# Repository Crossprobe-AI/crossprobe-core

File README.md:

# Crossprobe

A KiCad editor that runs in the browser. Open a KiCad project folder, view and
edit its schematic and board, and save it back as KiCad files: unmodified files
are written back byte for byte, and edits produce minimal diffs. The goal is
parity with KiCad: its behaviour is reimplemented in TypeScript and checked against
what KiCad itself does with the same projects.

Try it in your browser: <https://core.crossprobe.ai>, the editor from this
repository as it is. Files stay on your computer there too.

On a phone, the editor is a viewer: the schematic, the board and the 3D view, a tap on a part
for what it is, pinch to zoom.

## What it does

- Schematic, PCB and 3D views, with cross-probing between them.
- Schematic editing: wires, labels, buses, hierarchical sheets, parts from KiCad's
  libraries, annotation, ERC.
- PCB editing: placement, interactive routing (45° tracks, vias, differential pairs,
  length tuning), zones, Update PCB from schematic, DRC, schematic ↔ board parity.
- Symbol and footprint editors; plotting; fabrication outputs (Gerber, drill, BOM,
  pick-and-place, IPC-2581, ODB++, STEP, GLB).
- [Design blocks](blocks/README.md) (reference circuits with cited checklists),
  [requirements](docs/requirements.md) and [compatibility](docs/compatibility.md)
  checks, and datasheet evidence pinned to parts.

What works and what doesn't yet, feature by feature: [KiCad parity](#kicad-parity).

## Run it

With Docker ([docs/docker.md](docs/docker.md)):

```sh
docker compose up --build
```

Then open <http://localhost:5173> in Chrome, Edge or another Chromium browser and
choose your project's folder. Files stay on your computer: the browser reads the
folder and saves into it.

Without Docker, with Node.js 22.12 or later (KiCad's libraries are read from a KiCad
installation, or from `KICAD_SYMBOLS`, `KICAD_FOOTPRINTS` and `KICAD_DEMOS`):

```sh
npm ci
npm run dev         # the app at http://localhost:5173
```

To host it, build static files with `npm run build -w @crossprobe/web` (they land in
`apps/web/dist`). A build is served under `/app/`. Set `CROSSPROBE_BASE=/` to serve
it at the root of its own domain instead. The KiCad libraries are fetched from
`/__demos/…`, which the dev server answers; a static host has to provide them.

## Develop

How to contribute, and the rules a change follows: [CONTRIBUTING.md](CONTRIBUTING.md).
Bugs and requests: [GitHub Issues](https://github.com/Crossprobe-AI/crossprobe-core/issues). Security problems: privately, as
[SECURITY.md](SECURITY.md) says.

```sh
npm run build       # @crossprobe/kicad-sexpr and @crossprobe/kicad-model
npm run typecheck   # the app and its UI component tests
npm test
```

| Path | What it is |
|---|---|
| [`packages/kicad-sexpr`](packages/kicad-sexpr) | Lossless parser and writer for every KiCad S-expression format, with KiCad-style editing helpers |
| [`packages/kicad-model`](packages/kicad-model) | The design model: schematic hierarchy and nets as KiCad sees them, the board, ERC, DRC, parity, editing, fabrication outputs, design blocks |
| [`apps/web`](apps/web) | The browser app |
| [`apps/web/src/extensions`](apps/web/src/extensions/api.ts) | The editor's extension points: inspector tabs, places to open and keep projects, sections of the Review tab |

Many tests compare results with KiCad's own on its demo projects, and skip when
KiCad or the demos are missing. KiCad and its libraries are found in the usual
places on macOS and Linux ([test-setup.ts](test-setup.ts)). The demos are not
part of every installer: they are the `demos` folder of KiCad's source, so point
the tests at a copy.

| Variable | What it points at |
|---|---|
| `KICAD_CLI` | KiCad's command-line program, when it is not in the usual place |
| `KICAD_DEMOS` | KiCad's demo projects |
| `KICAD_CORPUS` | A folder of other projects to compare on, in place of the demos (the file round trip takes several, colon-separated) |
| `KICAD_QA` | The `qa/data` folder of KiCad's source, for the netlist edge cases |

The tests that compare with KiCad don't run on GitHub (the runner has no
KiCad): run `npm test` with the demos before changing the model, the checks or
the exports. The browser scripts in `scripts/e2e-*.mjs` drive the app end to
end ([docs/end-to-end.md](docs/end-to-end.md)).

The editor's shared controls (the top bar's menus, the inspector's tab bar,
Save) have component tests in `apps/web/test/ui/*.test.tsx`. They run in
headless Chromium with the app's stylesheet (Vitest's browser mode), so layout,
focus, keyboard and clicks are the real ones. `npm test` runs them with the rest;
the first time, install the browser with `npx playwright install chromium`.
`npx vitest --project ui` runs only them.

Commit messages follow [Conventional Commits](https://www.conventionalcommits.org)
(`fix:`, `feat:`, `feat!:` for a breaking change, and `docs:`, `test:`, `ci:`
for the rest). Releases are made from them: each push to `main` updates a release
pull request with the next version and the changelog, and merging it tags
`vX.Y.Z` and publishes the release
([release.yml](.github/workflows/release.yml)).

## KiCad parity

What a KiCad user can expect, compared with KiCad 9 and 10. The comparisons were
last run with KiCad 10.0.5. Update this list in the same change that adds or
completes a feature.

- **Works**: implemented, and checked against KiCad (a test or an end-to-end
  script compares the result with what KiCad gives for the same project).
- **Partly**: usable, with the limits given.
- **View only**: existing items are read, drawn, plotted and kept on save, but
  can't be made or changed here.
- **No**: not there. Unless noted, such items in an existing file are left
  untouched when you save, but are not shown.

### Files and projects

| Feature | Status | Notes |
|---|---|---|
| `.kicad_sch`, `.kicad_pcb` read and write | Works | Unchanged files are written back byte for byte; edits change only the lines they touch |
| Project symbol and footprint libraries (`.kicad_sym`, `.pretty`) | Works | Derived symbols are resolved |
| `.kicad_pro` | Partly | Net classes, design-rule minimums, severities, DRC exclusions and the pin conflict map are read and written; other settings are kept, with no way to edit them |
| New project, open a folder, save in place | Works | Saving in place needs a Chromium browser; others download the changed files. New files are written as KiCad 10 |
| Unsaved changes survive a reload | Works | |
| File versions before KiCad 9 | Works | KiCad 6, 7 and 8 files are read: every file in KiCad's own test data is written back byte for byte, and netlists (of annotated designs) and IPC-D-356 files match KiCad's on them. Edited and saved, all 113 of its files from before KiCad 8 are read by KiCad with every edit, and give KiCad's netlist |
| KiCad's installed libraries (symbols, footprints, 3D models) | Partly | Served by the dev server or the Docker image; your own path variables are not resolved |
| Library tables | Partly | Project tables with `${KIPRJMOD}` entries; no table editor |
| Custom design rules (`.kicad_dru`) | Partly | Read and applied for some constraints (see PCB editor); no editor |
| Text variables (`${REVISION}`, `${REFERENCE}`, project variables) | Partly | In the schematic, shown, plotted and netlisted as KiCad resolves them: the title block, sheet and project variables, a part's own fields, another part's (`${R1:VALUE}`). Not the net, pin and simulation variables (`${NET_NAME(1)}`, `${OP}`); on the board they are shown as written. No editor for project variables |
| Custom drawing sheets (`.kicad_wks`) | Partly | The project's sheet is drawn and plotted on every schematic page, its texts where KiCad puts them (checked on KiCad's templates and demos). Logos (PNG or JPEG) included. Chosen in KiCad: no picker here, no drawing sheet editor. The board view draws its own sheet (pcbnew's, from the project) around the board, with the board's title block, the project's text variables (as KiCad's board plot shows them) and a "Drawing sheet" visibility toggle; board plots leave it out. Both paths are resolved as KiCad does: `${KIPRJMOD}` and the project's text variables, relative or absolute into the project folder. A sheet outside the project folder (KiCad's template folder, say) can't be read in the browser. Without one, a default frame is drawn, its title block with the project's variables |
| Legacy formats (`.sch`, `.brd`, `.lib`), importers (Eagle, Altium, EasyEDA, …) | No | |
| Design variants, jobsets, embedded files, project templates and archives | No | |

### Schematic editor

| Feature | Status | Notes |
|---|---|---|
| Connectivity and net names as KiCad computes them | Works | Compared pin for pin and name for name with KiCad's netlist: hierarchy, buses, jumper pins and stacked pin numbers included |
| Wires, junctions, no-connects | Works | Dragging keeps connections |
| Buses, bus entries, vector buses | Works | Bus aliases are read; they can't be defined here |
| Local and hierarchical labels | Works | |
| Global labels | Works | With the shape (input, output, …) |
| Power symbols, PWR_FLAG | Works | |
| Hierarchical sheets and sheet pins | Works | A selected sheet symbol is renamed, given a page number, and its pins synchronised with the labels inside. Its file can't be changed, and its pins can't be moved or deleted one by one |
| Placing symbols from project and KiCad libraries | Works | |
| Multi-unit symbols | Works | |
| Body styles (De Morgan) | Works | Made in the symbol editor; a placed symbol is switched in the inspector |
| Alternate pin functions | Works | Defined per pin in the symbol editor (name, type, shape); a placed symbol's pin is switched in the inspector, and the sheet, ERC and netlist follow |
| Move, rotate, mirror, delete, box select, copy, paste, duplicate | Works | Its own clipboard: not the system's, not between projects |
| Undo and redo | Works | |
| Fields, and the symbol fields table | Works | A field on the sheet is dragged, turned (R) and edited (double-click) on its own, and shown or hidden in the inspector. No font or justification settings, no autoplace; no BOM presets |
| DNP, exclude from BOM, exclude from board, exclude from simulation | Works | A part not populated is crossed out, on the sheet and in plots |
| Annotation | Works | The whole schematic or one sheet; new parts only or all, by X or Y; from a start number or the sheet number × 100 or × 1000; clear annotation. No selection scope |
| Footprint assignment | Works | Filtered by the symbol's footprint filters and pin count |
| Text, text boxes, lines, rectangles, circles, arcs | Works | No font or style settings; beziers are view only |
| Images | Works | Placed with the Image tool (other formats become PNG, as KiCad stores them), moved, and sized; KiCad reads them back unchanged |
| Intersheet references | Works | The pages a global label is on, as KiCad lists them (own page, short form, prefix and suffix), switched on in Page settings; drawn where KiCad places them, not movable |
| Net class directives, rule areas | Works | Placed on wires and buses, or on a rule area's outline for everything inside; a label's Netclass field counts too. Nets get KiCad's classes, combined ones included ("A,Default"), and the project file keeps them as KiCad does. Only the Netclass field: no component classes |
| Tables | Works | Drawn as KiCad draws them (border, header line, separators, spans, text justified in each cell); placed with the Table tool (on sheets from KiCad 9 on), cells filled in by double-click, moved and box-selected as a whole, KiCad 9's tables (no UUID) too. Rows, columns and spans can't be changed here |
| Hyperlinks | Works | On texts and labels: a web address or a page (`#2`), opened with a click when not editing; set with Link… on a selected text. Not on fields or in plots |
| Find and replace | Works | Ctrl+F: texts, text boxes, labels, sheet names and pins, and fields, on every sheet; match case, whole words, wildcards, references, hidden fields. Replace all is one undo step. Not pin names or numbers |
| Cross-probing and net highlighting | Works | Between schematic, board and 3D |
| ERC | Partly | 33 checks, at least 98% agreement with KiCad on its demos, and 89% of KiCad's findings on the edge cases in its own test data: pin conflicts (with the project's pin map), undriven and unconnected pins, no-connect, label, wire, off-grid, multiple net names, similar labels, duplicate references, sheet pins and hierarchical labels without a partner, unplaced units (and their input, supply and bidirectional pins), units with different footprints, duplicate sheet names, a local label named like a global one, unresolved text variables (in texts), a global label that appears once, labels and power nets that differ only in case, field names with spaces around them. undefined net classes, a pin shared by a part's units on different nets, a ground pin off the ground net, a net label on a bus or a bus label on a wire, a wire through a bus entry that isn't one of the bus's members, two names on one bus. Not checked: bus-to-bus conflicts, bus alias conflicts, library and footprint link issues. Severities are read from the project. Findings can be excluded with a reason, kept in the project file as KiCad does: KiCad honours ours where the finding's items have UUIDs here (labels, pins), and we honour KiCad's by check, place and sheet |
| Netlist export | Works | KiCad's format (`.net`): the same parts, fields, nets and pins as `kicad-cli` writes on its demos. A net in several classes names the first. Not the OrcadPCB2, CadStar, Allegro, PADS, SPICE or XML formats |
| SPICE simulation | No | |
| Design blocks | Works | Inserts the blocks in `blocks/` and the project's own; a selection is saved as a block in the project's block library, in KiCad's layout (`<project>.kicad_blocks`, `design-block-lib-table`). No block library editor; blocks from other libraries in the table are not listed |
| Page settings and title block | Works | |
| Plot to SVG and PDF | Works | PDF through the browser's print dialog. No PostScript, DXF or HPGL |

### PCB editor

| Feature | Status | Notes |
|---|---|---|
| Place, move, rotate, flip, lock footprints | Works | Compared with KiCad's result for the same move |
| Update PCB from schematic, update schematic from PCB | Works | |
| Update footprints from the library | Works | |
| Schematic ↔ board parity, ratsnest | Works | A few zone-to-pad cases over-report unconnected items |
| Copper layer count, design-rule minimums, net classes | Works | With presets for KiCad's defaults and JLCPCB. A net in several classes (by pattern or from the schematic) combines them by priority, with Default filling what they leave unset, as KiCad 10 does |
| Stackup | Partly | Read and used; written only from the presets; no editor |
| Custom rules | Partly | `clearance`, `hole_size`, `annular_width`, `track_width`, `via_diameter`, `length` and `skew` (with `fromTo` between parts; skew `within_diff_pairs` too), `diff_pair_gap` and `diff_pair_uncoupled`, `connection_width`, with the common condition functions. Lengths between parts can differ from KiCad's by up to ~0.7 mm on some routes, so findings near a limit may differ; differential pair gaps and uncoupled lengths equal KiCad's. Not: edge, silk and courtyard clearance, `disallow` |
| Interactive routing with 45° tracks | Works | Posture, width, via and layer change while routing |
| Router modes | Partly | Highlight collisions and walkaround work; shove moves up to three tracks, along the grid |
| Arc tracks | View only | Drawn, measured and plotted; can't be routed |
| Dragging tracks | Partly | Track ends, and tracks follow a moved footprint; no segment drag |
| Vias: through, blind, buried, micro | Works | No tenting or via-in-pad options |
| Differential pairs | Partly | Coupled routing with paired vias; they don't shove |
| Length tuning | Partly | Single-track meanders to a target, and matching a pair; not saved as KiCad tuning patterns |
| Teardrops | Partly | Straight-edged; all or none |
| Zones: draw, fill, refill | Works | Priorities, thermal reliefs, island removal and keepouts are honoured; fills compared with KiCad's by area and by its DRC |
| Zone properties | Partly | Net, layer, pad connection, name, priority, clearance, minimum width, thermal gap and spoke width, island removal: edited in the properties panel, honoured by the fill, and read back by KiCad as set. Hatched fills (line width, gap, angle; KiCad's hole smoothing and minimum hole area as read) are filled as KiCad fills them, thermal rings round reliefs and same-net vias relieved too: on a demo zone made hatched, our copper differs from KiCad's by about as much as the solid fill does. Multi-layer zones keep their layer set; no corner smoothing or per-layer properties (nor per-layer hatch offsets) |
| Point editing of zones and shapes | Works | KiCad's handles on a selected zone, polygon, line, rectangle, circle or arc: corners, and edge middles that move an edge with its corners sliding along the neighbours; Add Corner and Remove Corner from the right-click menu. Outlines KiCad reads back as edited. Only a zone's first outline; no chamfer or fillet of corners |
| Keepout and rule areas | View only | Honoured by the fill, the DRC and custom rules |
| Board outline | Works | Rectangle, rounded rectangle, polygon, mounting holes |
| Graphics on other layers | View only | Movable; no drawing tools beyond the outline |
| Text | Partly | Silkscreen text can be placed and edited; knockout and TrueType text are view only |
| Dimensions | Partly | Aligned and orthogonal can be placed; radial, leader and centre are view only |
| Groups | Works | Group (Ctrl+G) and Ungroup (Ctrl+Shift+G), nested groups; a click selects a part's whole group, which moves, turns (about its centre: the box KiCad gives it, part texts and unmodelled items included, checked against pcbnew), aligns (by that box), locks (L) and deletes together, items the app doesn't model (images, tables, targets) included, locked ones staying; unlocking a group also unlocks its parts locked on their own; deleted items leave their groups and empty groups go. KiCad reads the groups back as made. Copies (duplicate, paste, array) are not grouped; no entering a group to edit one part |
| Text boxes | Works | Drawn with the text box tool (two corners, then the text), shown, plotted and wrapped as KiCad wraps them; turned, moved, aligned, and their text, size and layer edited. Plots match kicad-cli's (wrapping, every justification, turned, mirrored, with and without a border). Stroke font only; no knockout, margin or border editing |
| Images, tables | No | |
| DRC | Partly | Clearance and shorts; copper to edge and to hole; hole size, annular width, hole to hole; track width, via size; dangling tracks and vias; courtyard overlap, holes in another part's courtyard, missing and malformed courtyards, malformed board outline (shapes chained as KiCad chains them); overlapping zones of one net and priority; footprint type against its pads; footprints against their library copies (from the board toolbar's "Libraries"); starved thermals; silkscreen overlap and clipping; solder mask bridges; text size; keepouts (tracks and vias); minimum connection width (board setting or custom rule, A and B as KiCad evaluates them: KiCad's necks, on the same items; counts within a few percent). Not checked: copper slivers. Length and skew come from custom rules (see above). Severities are read from the project |
| DRC exclusions | Partly | KiCad honours ours only where the marker position equals its own |
| Net inspector | Works | Lengths per layer, vias, CSV. Lengths follow KiCad 10.0; KiCad 10.0.5 measures a few nets up to 0.2 mm shorter |
| Selection filter, layer visibility, flip view, measure tool | Works | No layer colours, presets or net colours |
| Copy, paste, duplicate | Works | Its own clipboard |
| Cleanup tracks and vias, geographic reannotation, board statistics | Works | |
| Pad properties | Partly | Size, shape, drill and net; not margins or zone connection |
| Logo footprint from a bitmap | Works | No smoothing |
| Align and distribute | Works | KiCad's ten commands, from the right-click menu: by bounding boxes (footprints without their text), locked items stay put and set the target, else the item under the cursor. Boxes compared with KiCad's on its demos; TrueType text is measured by its outlines |
| Arrays | Works | KiCad's Create Array (context menu; Ctrl+T where the browser passes it on): grids with offsets, stagger and fill order, circles with or without turning the items; copies get the next free references after their own, or keep them; or the selection itself is laid out. Copies compared with KiCad's pcbnew. No pad numbering (footprint editor) |
| Position relative | Works | KiCad's Position Relative To (Shift+P): the selection's top-left footprint to an item or point picked on the board, or the grid origin, plus an offset in x/y or polar; locked items stay. Positions compared with KiCad's. No local origin |
| DXF and SVG import, footprint wizard, component classes, repeated layout | No | |
| Python scripting, action plugins, the IPC API | No | |

### Symbol and footprint editors

| Feature | Status | Notes |
|---|---|---|
| Symbols: pins (all electrical types and shapes), pin table, body graphics, fields | Works | Beziers are view only |
| Symbols: units, unit names, body styles, jumper pin groups, power symbols | Works | |
| Symbols: update placed symbols from the library | Works | Wires on moved pins are not re-attached |
| Symbols: alternate pin functions | Works | Name, electrical type and shape per alternate |
| Symbols: derived symbols, import and export | No | Derived symbols in existing libraries are read |
| Footprints: pads singly, in rows and in grids; move, rotate, mirror, renumber | Works | Compared with KiCad's result |
| Footprints: pad types and shapes | Partly | SMD, through-hole and NPTH; rectangle, rounded rectangle, circle, oval, custom polygon. No trapezoid, chamfered or slotted pads |
| Footprints: mask and paste overrides, paste windows | Works | |
| Footprints: graphics on silkscreen, fab and courtyard; automatic courtyard | Works | No free text, fields only |
| Footprints: 3D model with offset, rotation, scale and a preview | Works | |
| Footprints: update placed footprints from the library | Works | Board toolbar's "Libraries" compares every footprint with its library copy as KiCad's DRC does (lib_footprint_mismatch): on KiCad's demos it flags exactly the footprints KiCad flags, and after updating them KiCad flags none |
| Symbol and footprint checks | Partly | Their own lists, not KiCad's checkers |
| Editing KiCad's own libraries, library management | No | A library part is copied into the project's library first |

### 3D viewer

| Feature | Status | Notes |
|---|---|---|
| Board with holes, copper, mask and silkscreen; STEP and VRML models | Works | Models placed as in KiCad's viewer; a missing model is shown as a box |
| Orbit, pan, zoom, view presets; click a part to select it | Works | |
| Layer visibility, colours, appearance presets | No | Parts can be hidden |
| Raytracing, render to an image | No | |

### Outputs

| Feature | Status | Notes |
|---|---|---|
| Gerber X2 | Works | Each layer within 1% of KiCad's plot by area. Fixed options; no X1 |
| Excellon drill files | Works | PTH, NPTH and a file per blind or buried span. No Gerber drill files, map or report |
| Gerber job file | Works | |
| Pick-and-place (CSV) | Works | Identical to KiCad's |
| BOM (CSV) | Partly | Grouped by value, footprint and part number; no presets |
| IPC-2581, ODB++ | Works | Compared with KiCad's by what CAM tools read |
| IPC-D-356 | Works | Byte-identical to KiCad's on its demo boards |
| STEP | Works | Volume within 0.1% of KiCad's; holes and arcs are polygons |
| GLB, STL, PLY | Works | |
| Board and schematic plots: SVG, PDF | Works | PDF through the browser's print dialog; few plot options |
| DXF, PostScript, HPGL, VRML, GenCAD, 3D PDF | No | |

### KiCad's other tools

| Feature | Status | Notes |
|---|---|---|
| Calculator | Partly | Track current and microstrip impedance, in Board setup |
| Gerber viewer, drawing sheet editor, plugin and content manager | No | |
| A command line like `kicad-cli` | No | `@crossprobe/kicad-model` can be used as a library from Node |
| Preferences, hotkey editor | No | Shortcuts follow KiCad's defaults |

### Not in KiCad

- An autorouter: single connections, and "Route all" with fan-out and stitching to
  pours.
- ERC, DRC and parity run after every edit; one-click fixes for common ERC findings.
- [Design blocks](blocks/README.md) with cited checklists, [requirements](docs/requirements.md)
  and [compatibility](docs/compatibility.md) checks, and datasheet evidence pinned to
  parts.
- Land patterns generated from datasheet dimensions.
- A pre-flight check before fabrication files are made, with JLCPCB presets and files.

## Licence

Apache-2.0 (see [LICENSE](LICENSE)). Third-party material keeps its own licence;
see [NOTICE](NOTICE). No KiCad source code is included: KiCad's behaviour is
reimplemented and compared with KiCad's results, never copied.

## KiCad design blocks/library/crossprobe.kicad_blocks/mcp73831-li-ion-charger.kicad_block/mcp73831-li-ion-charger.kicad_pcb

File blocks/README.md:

# Design blocks

Ready-made pieces of a design: a module with its reference circuit, a power
stage, an interface. Crossprobe stores them in **KiCad's own design-block
format** (KiCad 9+), so any KiCad user can add the library and use them there
too, and Crossprobe adds what KiCad's format has no place for: where each
value comes from, whether a person has checked it, and a checklist.

```
blocks/
  specs/                     the source of truth: one JSON per block
  images/                    <id>.svg (cropped schematic, for the page) and <id>.png (1200x630, social preview)
  library/
    crossprobe.kicad_blocks/                  a KiCad design-block library
      <id>.kicad_block/
        <id>.kicad_sch                        the schematic (KiCad)
        <id>.json                             description + keywords (KiCad)
        <id>.crossprobe.json                  sources, review status, parts, checklist (Crossprobe)
```

The files under `library/` and `images/` are generated and committed, so a
change is an ordinary diff. Images need `kicad-cli` and `rsvg-convert`; without
them the build skips them and keeps the committed ones.

## Public repository

The library is published to
[github.com/Crossprobe-AI/kicad-design-blocks](https://github.com/Crossprobe-AI/kicad-design-blocks)
on every change. Its README is generated from the `.crossprobe.json` files, so
edit blocks here, never there.

## How a block is made

1. **Draft a spec** (`blocks/specs/<id>.json`): the parts (KiCad symbol,
   value, footprint), the net each pin goes to, notes for the sheet, and a
   checklist, plus the `seo` title and description for its public page. AI can
   draft this from the datasheet. Every part and checklist
   item names its **source** (document and page) or is marked
   `"basis": "convention"` when it is common practice rather than something
   the document says.
2. **Generate:** `node scripts/build-blocks.mjs` (needs `npm run build` and
   KiCad's symbol libraries) turns the spec into the schematic in KiCad's
   layout, then checks it: citations resolve, and the schematic's nets, read
   with the same connectivity code the app uses, are exactly the spec's.
   Output is deterministic: rebuilding changes nothing. `--check` fails if
   the committed library is out of date.
3. **Review:** a person compares each value with its cited page and the
   rendered schematic, then sets `"status": "reviewed"`, `reviewedBy` and
   `reviewedAt`. Until then the block is a `draft` and is shown as one.
4. **Tests** (`npm test`) use KiCad as the oracle: KiCad must load every
   block, its netlist must equal the spec, and ERC may report only the
   unavoidable "power input not driven" (a block has no supply). Inserting a
   block into a KiCad demo project must give a netlist that KiCad and our code
   agree on.

## Using a block

`insertBlock` (in `@crossprobe/kicad-model`) copies a block's schematic into a
sheet with its library symbols, gives new parts references like `C?` and
instance data for the target project; `planAnnotation` in `unannotated` mode
then numbers them. Items that touch existing wires join their nets, so
`findFreeSpot` finds empty space below the sheet's content.

## Rules for content

- **Cite or label.** A claim from a document needs a page; anything else is
  `convention`. The checklist separates what is *required* by the datasheet
  from *recommended* practice and *info*.
- **Don't copy documents.** Values and pin assignments are facts, quoted with
  page numbers. Schematics are redrawn from KiCad's own symbols; text from a
  datasheet is not reproduced beyond short quotes.
- **Licenses.** Blocks are Apache-2.0. KiCad's symbols and footprints are
  CC-BY-SA 4.0 with KiCad's exception for designs that use them. Espressif's
  hardware guidelines are Apache-2.0; its datasheets are not, so we cite them.
- **Datasheet versions change.** Each source names the version it was read
  from. Re-check a block when the datasheet is revised.

## Blocks

| Block | Status | Source |
|---|---|---|
| `esp32-s3-wroom-1-minimal`: ESP32-S3-WROOM-1 module with decoupling, EN reset network and button, USB, UART, JTAG and boot header | draft | Espressif datasheet v1.8, Figure 9-1 |
| `esp32-c3-wroom-02-minimal`: ESP32-C3-WROOM-02 module with decoupling, EN reset network and button, boot-strap pull-ups, USB, UART, JTAG and boot header | draft | Espressif datasheet v1.7, Figure 9-1 |
| `rp2040-minimal`: RP2040 with decoupling, internal regulator capacitors, W25Q128JVS flash, 12 MHz crystal, USB and BOOTSEL | draft | Raspberry Pi, Hardware design with RP2040; MIT design files R3-S1 |
| `ap2112k-3v3-ldo`: 3.3 V, 600 mA LDO from 5 V | draft | Diodes AP2112 datasheet, DS39724 Rev. 2-2 |
| `mcp73831-li-ion-charger`: single-cell Li-ion charger, 500 mA | draft | Microchip MCP73831/2 datasheet, DS20001984H |
| `usb-c-power-input`: USB-C receptacle as a 5 V sink with USB 2.0 data | draft | USB Type-C Cable and Connector Specification, Release 2.0 |

Blocks combine: take 3.3 V for the RP2040 or ESP32 block from the LDO block.

## PCB layouts

A spec may carry a `layout`: part positions, tracks and vias (mm, KiCad board
coordinates), plus layout rules with the same citation rules as the checklist.
The build writes `<id>.kicad_pcb` next to the schematic and a layout picture
(`blocks/images/<id>-pcb.svg`). KiCad's DRC with schematic parity must pass:
the only findings allowed are the missing board outline (a block takes the
board it is placed on) and, for modules, drill sizes and library-mismatch
notes that come from KiCad's own footprint.

| Block | Layout |
|---|---|
| `ap2112k-3v3-ldo`, `mcp73831-li-ion-charger`, `usb-c-power-input` | placed and routed |
| `esp32-s3-wroom-1-minimal`, `esp32-c3-wroom-02-minimal` | placement (`"routed": false`) with antenna keep-out clear, plus the critical nets routed: 3V3 decoupling, ground pin, EN reset network; the rest is a ratsnest |
| `rp2040-minimal` | placement only: decoupling at the supply pins, crystal at XIN/XOUT, flash near the QSPI pins; nothing routed (0.4 mm pitch fan-out depends on your rules) |

`fabReferences` puts reference designators on the fab layer in dense placements.

"Add block" in the app and "Open in Crossprobe" put the footprints (and
copper, when the block is routed) on the project's board, linked to the new
schematic symbols. Layouts are drafts too: review them with the schematic.

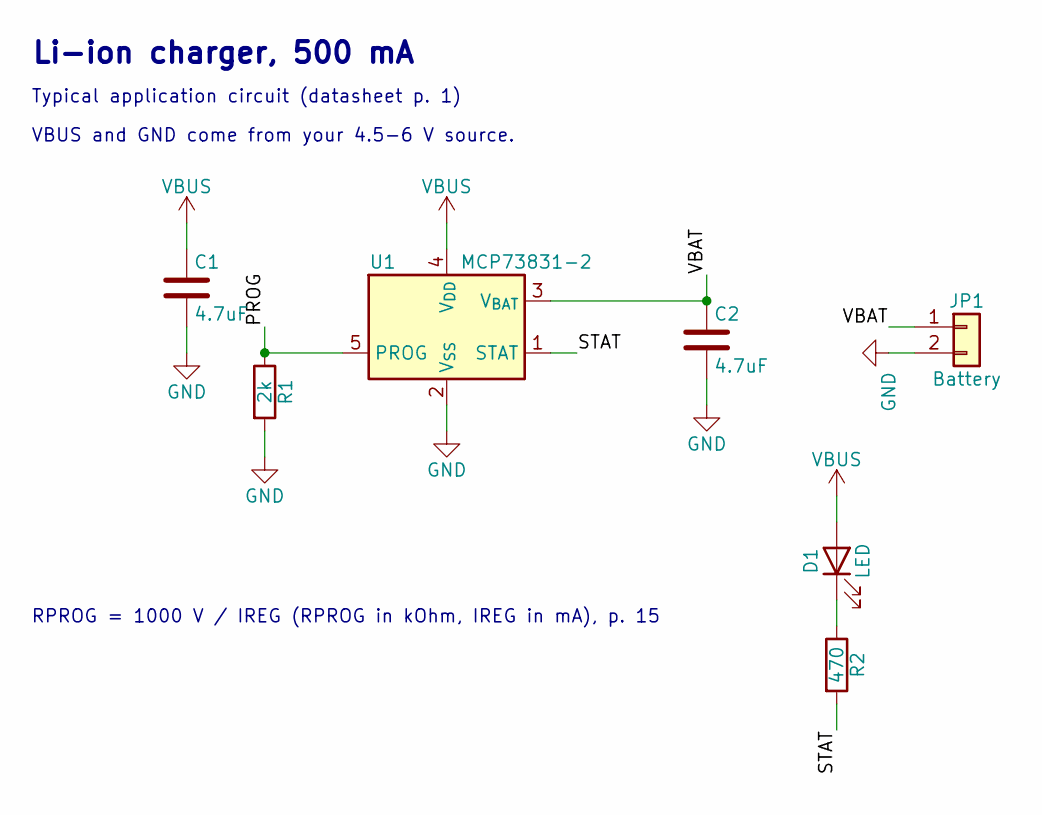
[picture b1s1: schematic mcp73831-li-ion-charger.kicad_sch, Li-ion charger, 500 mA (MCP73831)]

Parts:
C1, C2: 4.7uF; C_0805_2012Metric
D1: LED; LED_0603_1608Metric
JP1: Battery; JST_PH_B2B-PH-K_1x02_P2.00mm_Vertical
R1: 2k; R_0603_1608Metric
R2: 470; R_0603_1608Metric
U1: MCP73831-2; SOT-23-5

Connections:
/PROG: R1.1, U1.5 (PROG)
/STAT: R2.2, U1.1 (STAT)
/VBAT: C2.1, JP1.1, U1.3 (V_{BAT})
GND: C1.2, C2.2, JP1.2, R1.2, U1.2 (V_{SS})
unnamed: D1.1 (K), R2.1
VBUS: C1.1, D1.2 (A), U1.4 (V_{DD})

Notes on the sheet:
Li-ion charger, 500 mA
Typical application circuit (datasheet p. 1)
VBUS and GND come from your 4.5-6 V source.
RPROG = 1000 V / IREG (RPROG in kOhm, IREG in mA), p. 15

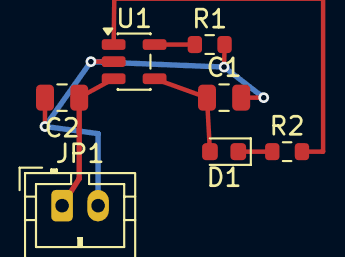
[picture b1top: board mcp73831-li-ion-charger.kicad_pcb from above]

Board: 2 copper layers, 7 parts (0 on the bottom side), 6 nets.

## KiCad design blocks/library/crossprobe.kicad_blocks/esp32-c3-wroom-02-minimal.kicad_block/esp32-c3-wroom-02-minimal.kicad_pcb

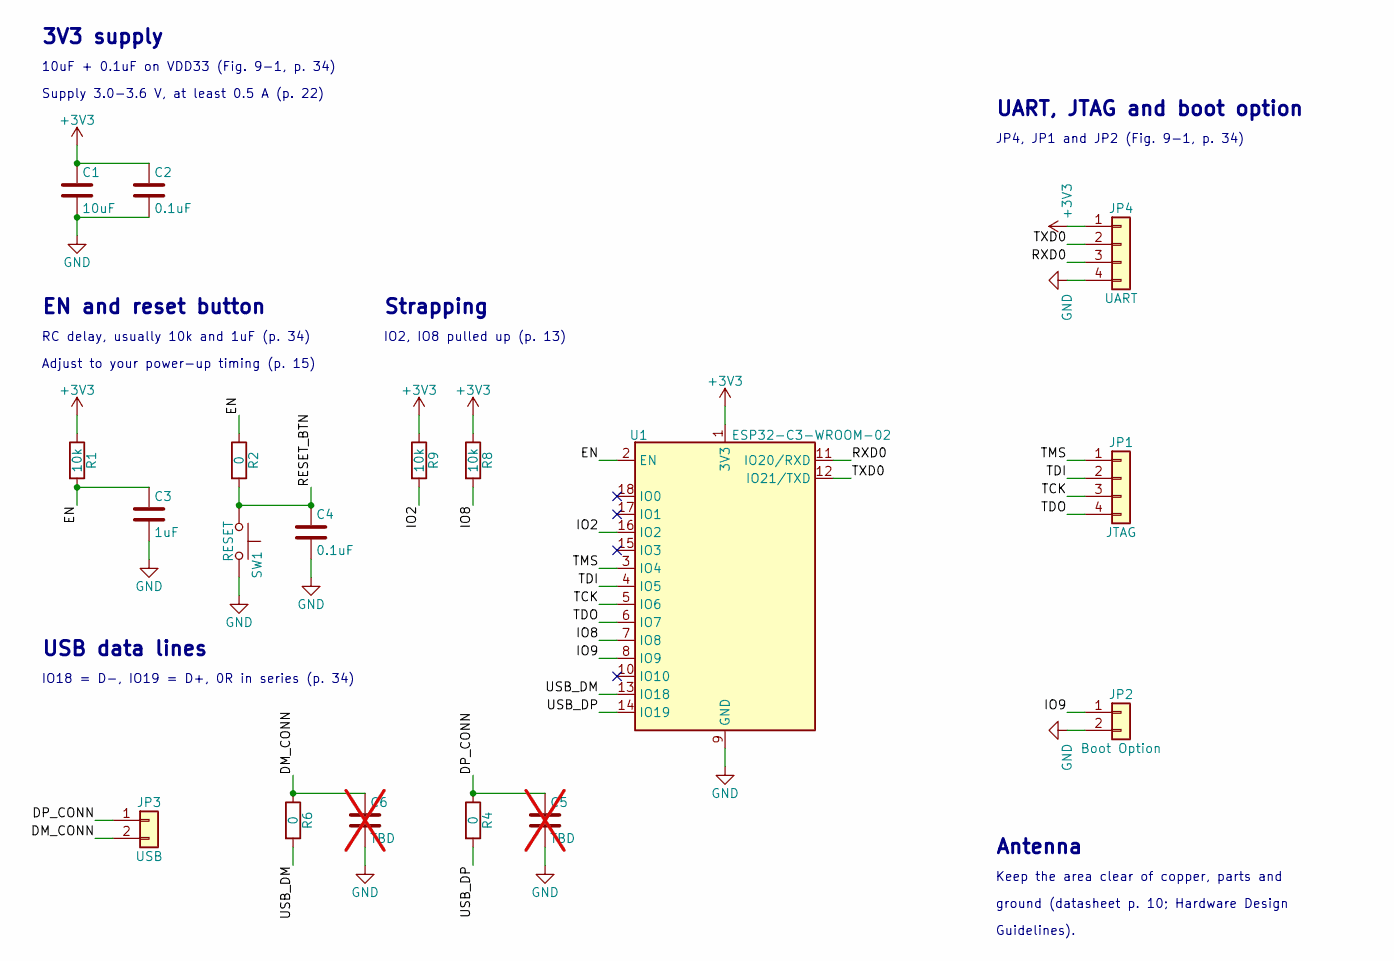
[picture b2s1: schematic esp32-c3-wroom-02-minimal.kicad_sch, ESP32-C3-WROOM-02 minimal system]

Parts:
C1: 10uF; C_0805_2012Metric
C2, C4: 0.1uF; C_0603_1608Metric
C3: 1uF; C_0603_1608Metric
C5, C6: TBD; C_0603_1608Metric; not fitted
JP1: JTAG; PinHeader_1x04_P2.54mm_Vertical
JP2: Boot Option; PinHeader_1x02_P2.54mm_Vertical
JP3: USB; PinHeader_1x02_P2.54mm_Vertical
JP4: UART; PinHeader_1x04_P2.54mm_Vertical
R1, R8, R9: 10k; R_0603_1608Metric
R2, R4, R6: 0; R_0603_1608Metric
SW1: RESET; SW_Push_1P1T_NO_CK_KMR2
U1: ESP32-C3-WROOM-02

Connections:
+3V3: C1.1, C2.1, JP4.1, R1.1, R8.1, R9.1, U1.1 (3V3)
/DM_CONN: C6.1, JP3.2, R6.1
/DP_CONN: C5.1, JP3.1, R4.1
/EN: C3.1, R1.2, R2.1, U1.2 (EN)
/IO2: R9.2, U1.16 (IO2)
/IO8: R8.2, U1.7 (IO8)
/IO9: JP2.1, U1.8 (IO9)
/RESET_BTN: C4.1, R2.2, SW1.1
/RXD0: JP4.3, U1.11 (IO20/RXD)
/TCK: JP1.3, U1.5 (IO6)
/TDI: JP1.2, U1.4 (IO5)
/TDO: JP1.4, U1.6 (IO7)
/TMS: JP1.1, U1.3 (IO4)
/TXD0: JP4.2, U1.12 (IO21/TXD)
/USB_DM: R6.2, U1.13 (IO18)
/USB_DP: R4.2, U1.14 (IO19)
GND: C1.2, C2.2, C3.2, C4.2, C5.2, C6.2, JP2.2, JP4.4, SW1.2, U1.9 (GND), U1.19 (GND)

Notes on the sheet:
3V3 supply
10uF + 0.1uF on VDD33 (Fig. 9-1, p. 34)
Supply 3.0-3.6 V, at least 0.5 A (p. 22)
EN and reset button
RC delay, usually 10k and 1uF (p. 34)
Adjust to your power-up timing (p. 15)
Strapping
IO2, IO8 pulled up (p. 13)
USB data lines
IO18 = D-, IO19 = D+, 0R in series (p. 34)
UART, JTAG and boot option
JP4, JP1 and JP2 (Fig. 9-1, p. 34)
Antenna
Keep the area clear of copper, parts and
ground (datasheet p. 10; Hardware Design
Guidelines).

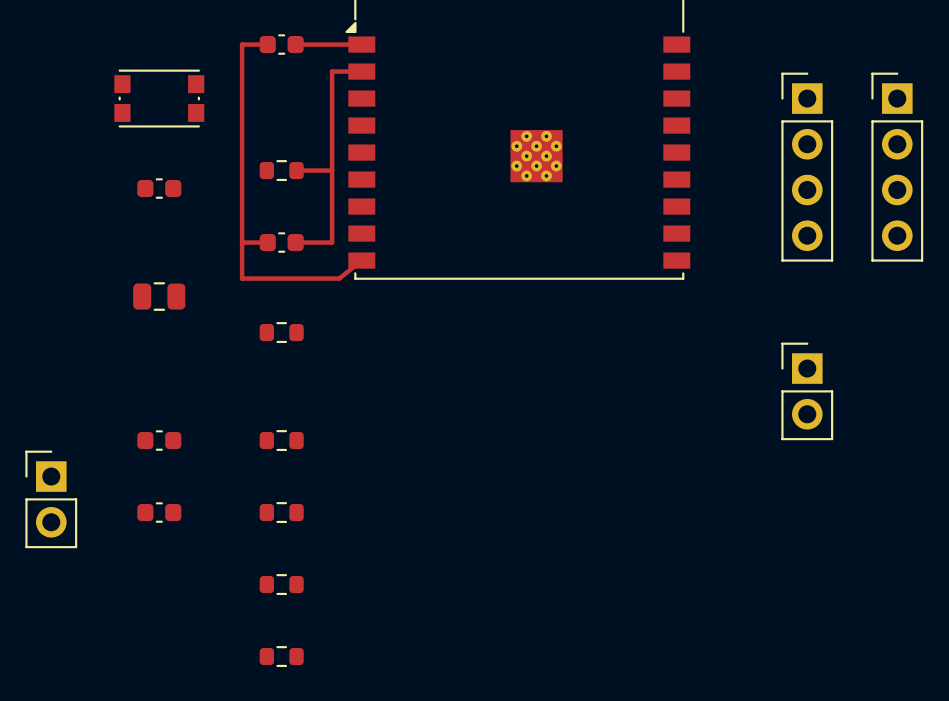
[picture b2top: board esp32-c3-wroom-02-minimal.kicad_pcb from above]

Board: 2 copper layers, 18 parts (0 on the bottom side), 17 nets.

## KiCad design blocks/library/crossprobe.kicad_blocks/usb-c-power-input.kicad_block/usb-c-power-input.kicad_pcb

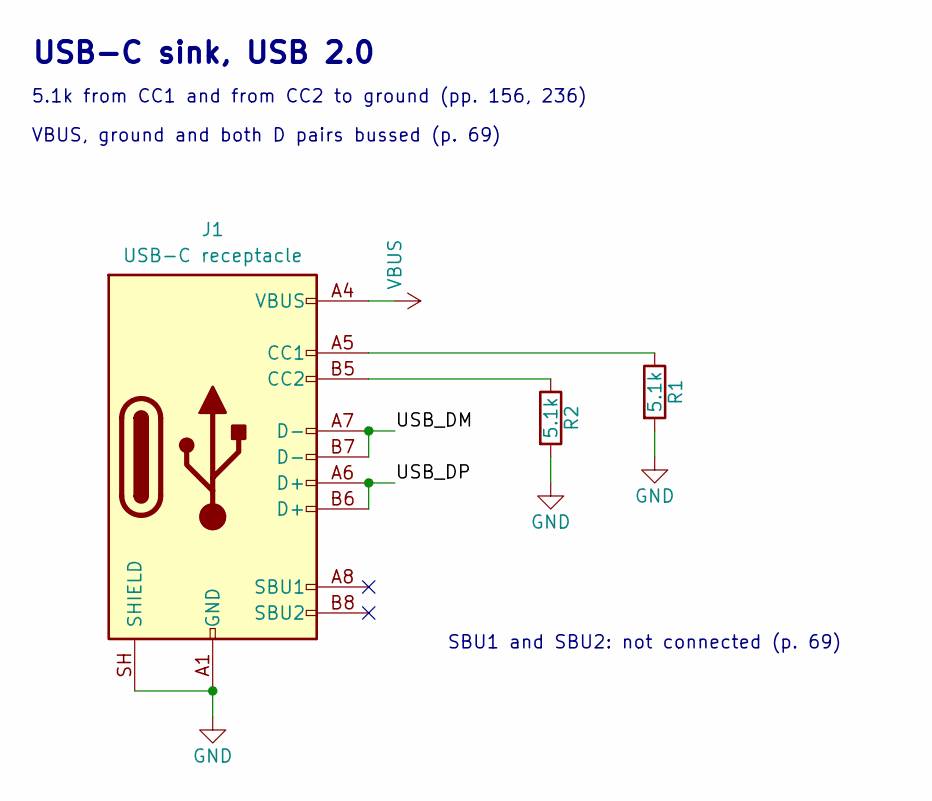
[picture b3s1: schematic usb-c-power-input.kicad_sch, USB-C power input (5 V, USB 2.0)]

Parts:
J1: USB-C receptacle; USB_C_Receptacle_HRO_TYPE-C-31-M-12
R1, R2: 5.1k; R_0402_1005Metric

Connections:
/USB_DM: J1.A7 (D-), J1.B7 (D-)
/USB_DP: J1.A6 (D+), J1.B6 (D+)
GND: J1.A1 (GND), J1.A12 (GND), J1.B1 (GND), J1.B12 (GND), J1.SH (SHIELD), R1.2, R2.2
unnamed: J1.A5 (CC1), R1.1
unnamed: J1.B5 (CC2), R2.1
VBUS: J1.A4 (VBUS), J1.A9 (VBUS), J1.B4 (VBUS), J1.B9 (VBUS)

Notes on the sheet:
USB-C sink, USB 2.0
5.1k from CC1 and from CC2 to ground (pp. 156, 236)
VBUS, ground and both D pairs bussed (p. 69)
SBU1 and SBU2: not connected (p. 69)

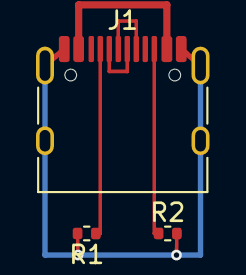
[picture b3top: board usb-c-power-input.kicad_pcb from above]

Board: 2 copper layers, 3 parts (0 on the bottom side), 6 nets.

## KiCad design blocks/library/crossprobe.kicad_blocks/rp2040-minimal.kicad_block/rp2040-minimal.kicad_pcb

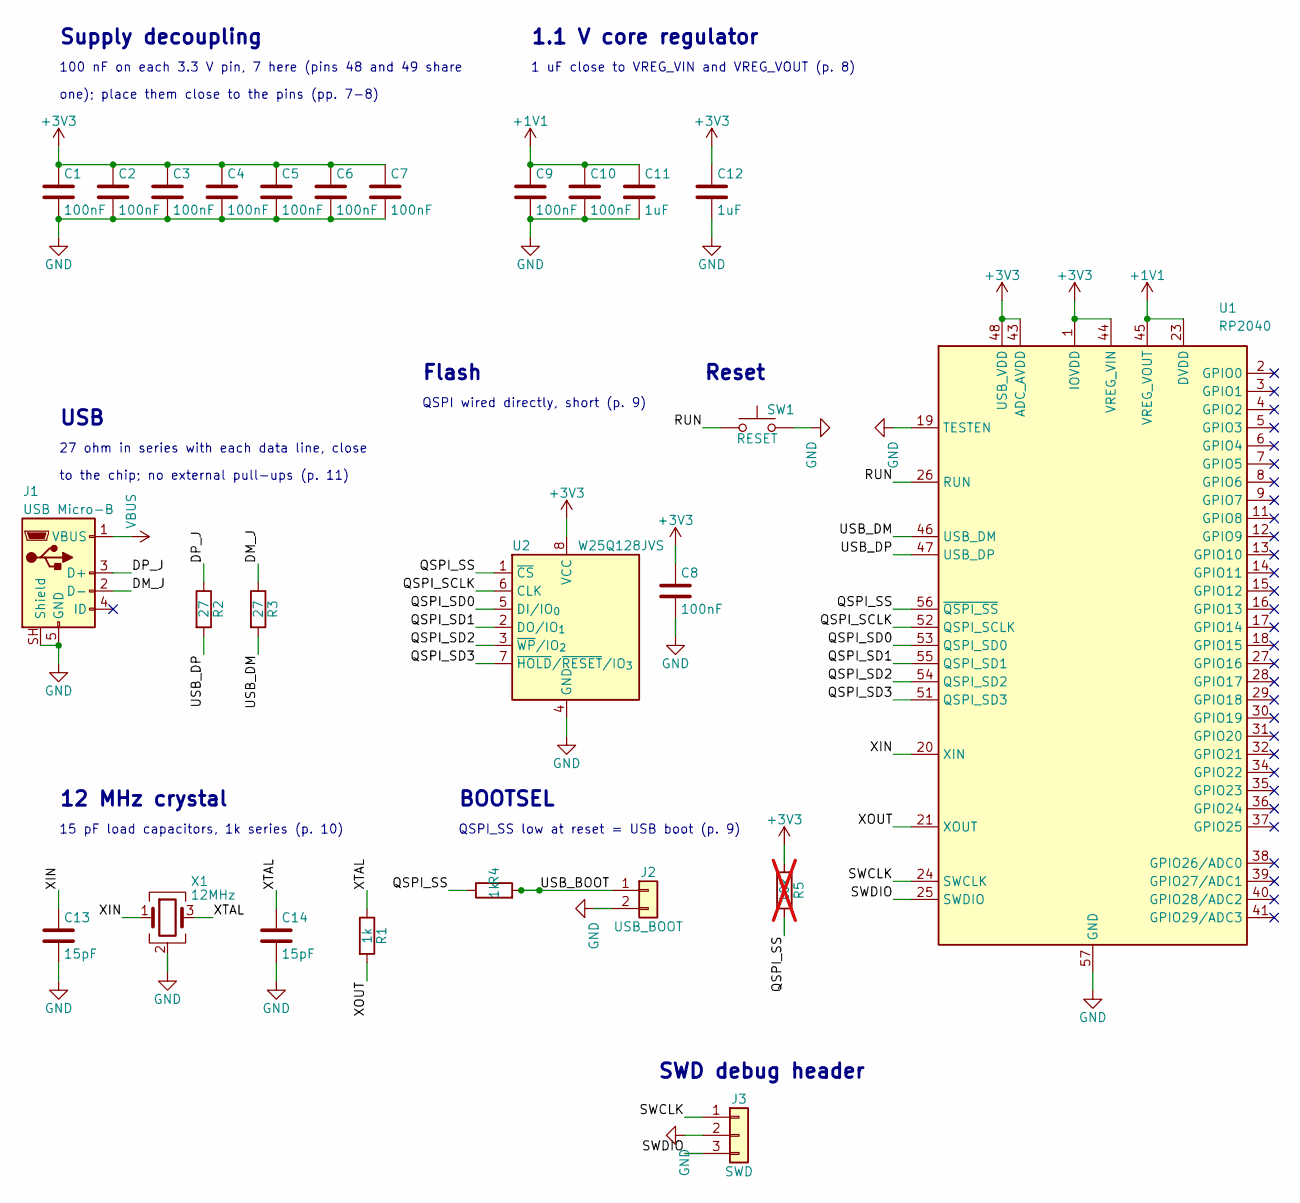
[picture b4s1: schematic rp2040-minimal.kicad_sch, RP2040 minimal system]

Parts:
C1, C2, C3, C4, C5, C6, C7, C8, C9, C10: 100nF; C_0402_1005Metric
C11, C12: 1uF; C_0402_1005Metric
C13, C14: 15pF; C_0402_1005Metric
J1: USB Micro-B; USB_Micro-B_Amphenol_10103594-0001LF_Horizontal
J2: USB_BOOT; PinHeader_1x02_P2.54mm_Vertical
J3: SWD; PinHeader_1x03_P2.54mm_Vertical
R1, R4: 1k; R_0402_1005Metric
R2, R3: 27; R_0402_1005Metric
R5: 10k; R_0402_1005Metric; not fitted
SW1: RESET; SW_Push_1P1T_NO_CK_KMR2
U1: RP2040; QFN-56-1EP_7x7mm_P0.4mm_EP3.2x3.2mm
U2: W25Q128JVS; SOIC-8_5.3x5.3mm_P1.27mm
X1: 12MHz; Crystal_SMD_3225-4Pin_3.2x2.5mm

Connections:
+1V1: C9.1, C10.1, C11.1, U1.23 (DVDD), U1.45 (VREG_VOUT), U1.50 (DVDD)
+3V3: C1.1, C2.1, C3.1, C4.1, C5.1, C6.1, C7.1, C8.1, C12.1, R5.1, U1.1 (IOVDD), U1.10 (IOVDD), U1.22 (IOVDD), U1.33 (IOVDD), U1.42 (IOVDD), U1.43 (ADC_AVDD), U1.44 (VREG_VIN), U1.48 (USB_VDD), U1.49 (IOVDD), U2.8 (VCC)
/DM_J: J1.2 (D-), R3.1
/DP_J: J1.3 (D+), R2.1
/QSPI_SCLK: U1.52 (QSPI_SCLK), U2.6 (CLK)
/QSPI_SD0: U1.53 (QSPI_SD0), U2.5 (DI/IO_{0})
/QSPI_SD1: U1.55 (QSPI_SD1), U2.2 (DO/IO_{1})
/QSPI_SD2: U1.54 (QSPI_SD2), U2.3 (~WP/IO_{2})
/QSPI_SD3: U1.51 (QSPI_SD3), U2.7 (~HOLD/~RESET/IO_{3})
/QSPI_SS: R4.1, R5.2, U1.56 (~QSPI_SS), U2.1 (~CS)
/RUN: SW1.1, U1.26 (RUN)
/SWCLK: J3.1, U1.24 (SWCLK)
/SWDIO: J3.3, U1.25 (SWDIO)
/USB_BOOT: J2.1, R4.2
/USB_DM: R3.2, U1.46 (USB_DM)
/USB_DP: R2.2, U1.47 (USB_DP)
/XIN: C13.1, U1.20 (XIN), X1.1
/XOUT: R1.2, U1.21 (XOUT)
/XTAL: C14.1, R1.1, X1.3
GND: C1.2, C2.2, C3.2, C4.2, C5.2, C6.2, C7.2, C8.2, C9.2, C10.2, C11.2, C12.2, C13.2, C14.2, J1.5 (GND), J1.SH (Shield), J2.2, J3.2, SW1.2, U1.19 (TESTEN), U1.57 (GND), U2.4 (GND), X1.2 (G), X1.4 (G)
VBUS: J1.1 (VBUS)

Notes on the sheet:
Supply decoupling
100 nF on each 3.3 V pin, 7 here (pins 48 and 49 share
one); place them close to the pins (pp. 7-8)
1.1 V core regulator
1 uF close to VREG_VIN and VREG_VOUT (p. 8)
USB
27 ohm in series with each data line, close
to the chip; no external pull-ups (p. 11)
Flash
QSPI wired directly, short (p. 9)
12 MHz crystal
15 pF load capacitors, 1k series (p. 10)
BOOTSEL
QSPI_SS low at reset = USB boot (p. 9)
Reset
SWD debug header

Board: 2 copper layers, 26 parts (0 on the bottom side), 20 nets, no tracks yet.

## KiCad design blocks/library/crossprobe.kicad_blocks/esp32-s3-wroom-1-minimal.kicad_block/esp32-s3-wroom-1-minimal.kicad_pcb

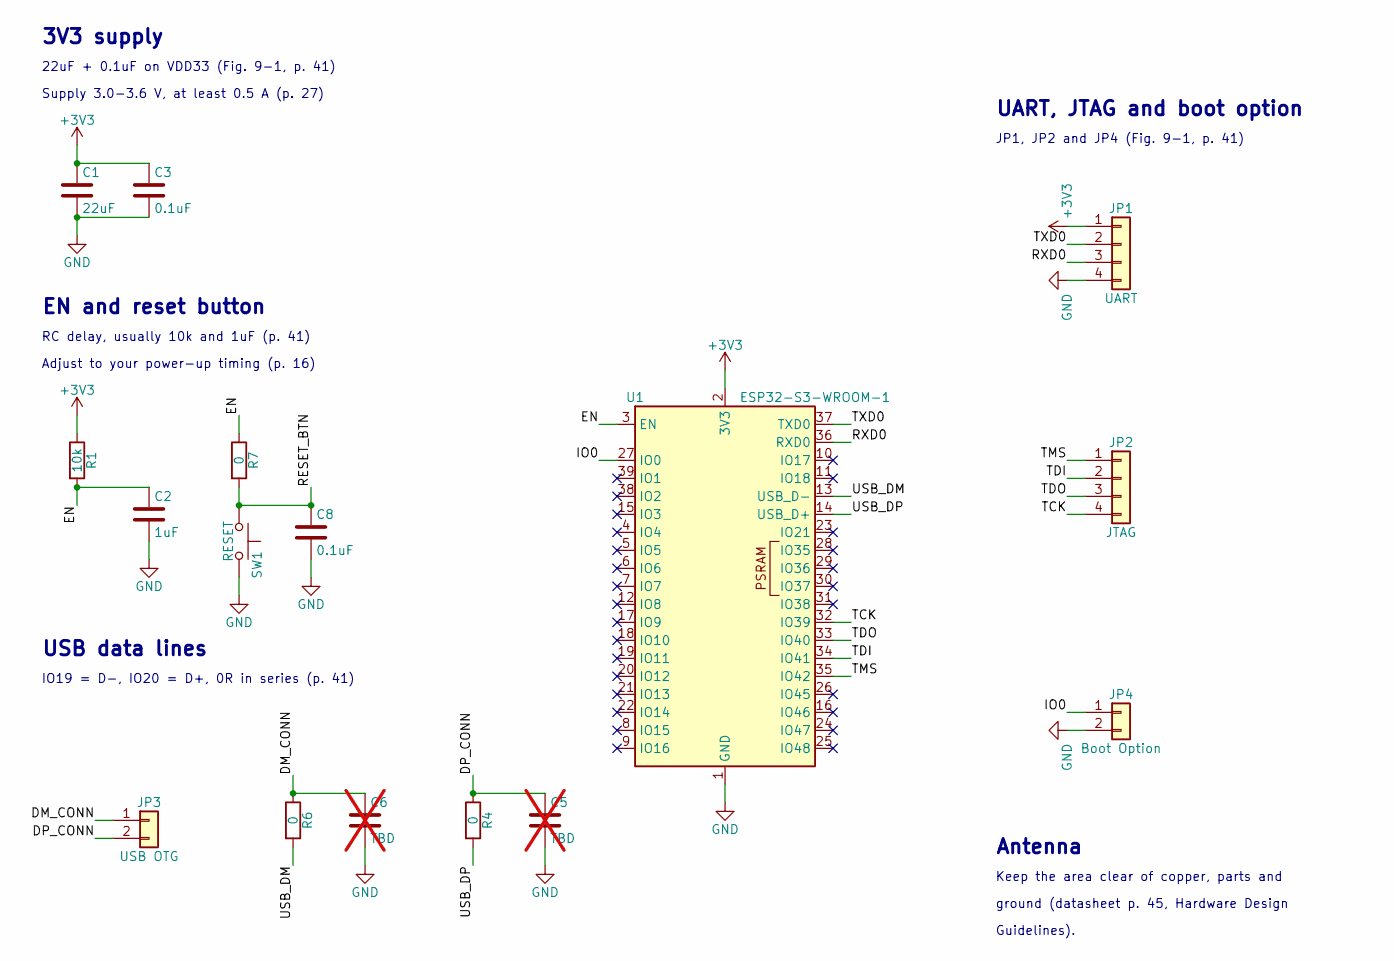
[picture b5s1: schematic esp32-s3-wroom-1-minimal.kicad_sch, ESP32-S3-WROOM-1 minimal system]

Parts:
C1: 22uF; C_0805_2012Metric
C2: 1uF; C_0603_1608Metric
C3, C8: 0.1uF; C_0603_1608Metric
C5, C6: TBD; C_0603_1608Metric; not fitted
JP1: UART; PinHeader_1x04_P2.54mm_Vertical
JP2: JTAG; PinHeader_1x04_P2.54mm_Vertical
JP3: USB OTG; PinHeader_1x02_P2.54mm_Vertical
JP4: Boot Option; PinHeader_1x02_P2.54mm_Vertical
R1: 10k; R_0603_1608Metric
R4, R6, R7: 0; R_0603_1608Metric
SW1: RESET; SW_Push_1P1T_NO_CK_KMR2
U1: ESP32-S3-WROOM-1

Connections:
+3V3: C1.1, C3.1, JP1.1, R1.1, U1.2 (3V3)
/DM_CONN: C6.1, JP3.1, R6.1
/DP_CONN: C5.1, JP3.2, R4.1
/EN: C2.1, R1.2, R7.1, U1.3 (EN)
/IO0: JP4.1, U1.27 (IO0)
/RESET_BTN: C8.1, R7.2, SW1.1
/RXD0: JP1.3, U1.36 (RXD0)
/TCK: JP2.4, U1.32 (IO39)
/TDI: JP2.2, U1.34 (IO41)
/TDO: JP2.3, U1.33 (IO40)
/TMS: JP2.1, U1.35 (IO42)
/TXD0: JP1.2, U1.37 (TXD0)
/USB_DM: R6.2, U1.13 (USB_D-)
/USB_DP: R4.2, U1.14 (USB_D+)
GND: C1.2, C2.2, C3.2, C5.2, C6.2, C8.2, JP1.4, JP4.2, SW1.2, U1.1 (GND), U1.40 (GND), U1.41 (GND)

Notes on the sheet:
3V3 supply
22uF + 0.1uF on VDD33 (Fig. 9-1, p. 41)
Supply 3.0-3.6 V, at least 0.5 A (p. 27)
EN and reset button
RC delay, usually 10k and 1uF (p. 41)
Adjust to your power-up timing (p. 16)
USB data lines
IO19 = D-, IO20 = D+, 0R in series (p. 41)
UART, JTAG and boot option
JP1, JP2 and JP4 (Fig. 9-1, p. 41)
Antenna
Keep the area clear of copper, parts and
ground (datasheet p. 45, Hardware Design
Guidelines).

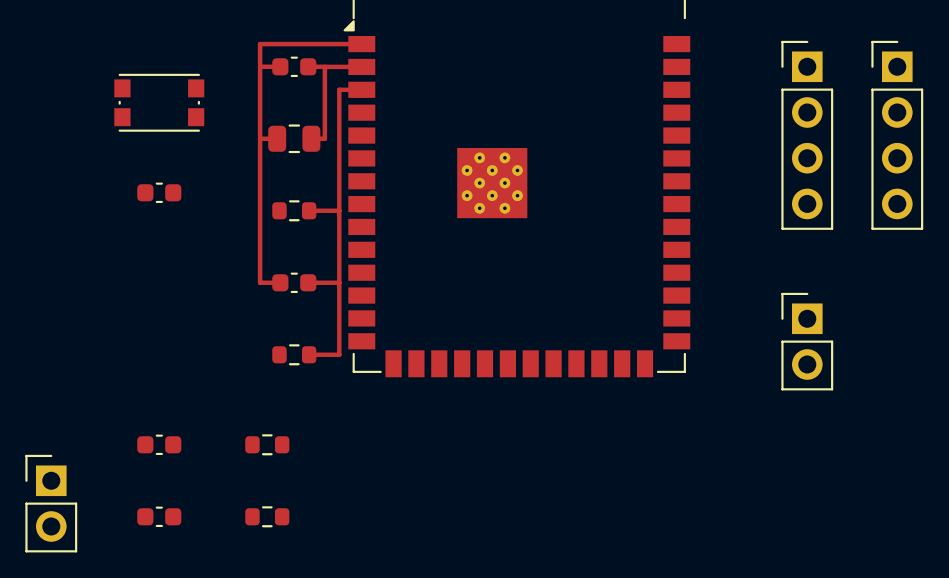
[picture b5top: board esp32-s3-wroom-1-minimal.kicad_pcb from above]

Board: 2 copper layers, 16 parts (0 on the bottom side), 15 nets.

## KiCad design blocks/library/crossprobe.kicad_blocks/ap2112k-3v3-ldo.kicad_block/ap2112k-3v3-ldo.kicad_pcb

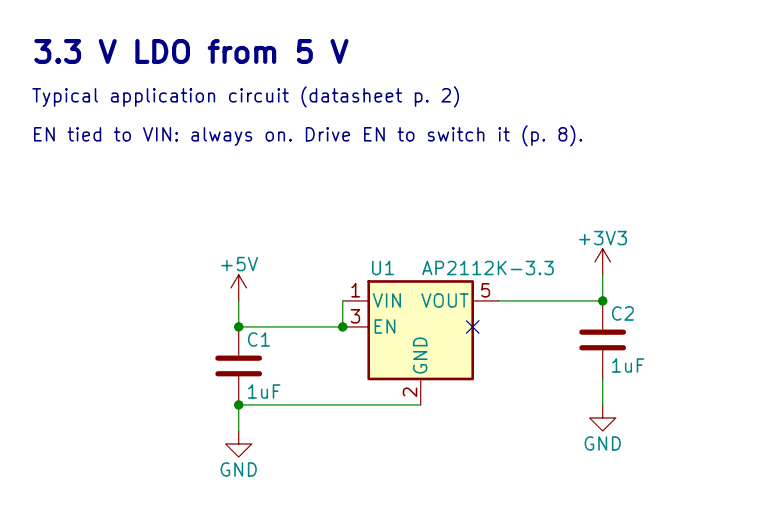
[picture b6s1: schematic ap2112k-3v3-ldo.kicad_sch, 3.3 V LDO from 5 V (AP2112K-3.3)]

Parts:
C1, C2: 1uF; C_0603_1608Metric
U1: AP2112K-3.3; SOT-23-5

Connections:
+3V3: C2.1, U1.5 (VOUT)
+5V: C1.1, U1.1 (VIN), U1.3 (EN)
GND: C1.2, C2.2, U1.2 (GND)

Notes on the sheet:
3.3 V LDO from 5 V
Typical application circuit (datasheet p. 2)
EN tied to VIN: always on. Drive EN to switch it (p. 8).

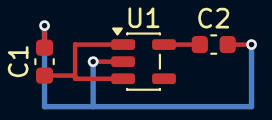
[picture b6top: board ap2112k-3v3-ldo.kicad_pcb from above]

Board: 2 copper layers, 3 parts (0 on the bottom side), 3 nets.

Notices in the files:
README.md:
License: Apache-2.0
